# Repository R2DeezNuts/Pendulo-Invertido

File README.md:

# Péndulo invertido: control PID e interfaz web

Sistema de control PID para estabilizar un péndulo invertido con un ESP32. Incluye una interfaz web para ajustar los parámetros, telemetría y rutinas de calibración.

## Características

- Control PID a 100 Hz.
- Ajuste remoto de Kp, Ki, Kd, setpoint y offset.
- Calibración del ángulo cero.
- Desactivación automática cuando detecta una caída.
- Telemetría del estado del sistema.
- Anti-windup para limitar la acumulación del término integral.

## Hardware

- **Microcontrolador:** ESP32
- **Sensor inercial:** MPU6050 (acelerómetro y giroscopio)
- **Actuadores:** dos motores DC con puente H

### Conexiones GPIO

#### MPU6050 (I2C)

| Señal | GPIO |
|------:|:----:|
| SDA   | 21   |
| SCL   | 22   |

#### Motores (puente H)

| Motor | Señal | GPIO |
|------:|:-----:|
| A     | PWMA  | 26   |
| A     | AIN1  | 2    |
| A     | AIN2  | 0    |
| B     | PWMB  | 25   |
| B     | BIN1  | 16   |
| B     | BIN2  | 17   |

## Puesta en marcha

1. Conéctate a la red WiFi **RobotAP** (contraseña: 12345678).
2. Abre http://192.168.4.1 en el navegador.
3. Con el robot en posición vertical, calibra el ángulo cero antes de activar los motores.
4. Ajusta los parámetros PID desde la interfaz y activa el control.

## Parámetros ajustables

| Parámetro | Descripción |
|----------:|-------------|
| **Kp, Ki, Kd** | Constantes del controlador PID |
| **Setpoint** | Ángulo objetivo, en grados |
| **Offset** | Ajuste fino para la calibración |

## Protección y arquitectura

La protección desactiva el control cuando el ángulo supera los 30° durante más de un segundo. El control se ejecuta en una tarea de FreeRTOS a 100 Hz; el servidor web permite consultar el estado y cambiar los parámetros; y un filtro complementario combina el acelerómetro y el giroscopio para estimar el ángulo.

## Uso recomendado

Coloca el robot en vertical, calibra el sensor y empieza con valores PID conservadores. Activa los motores mientras observas la telemetría y ajusta el setpoint y el offset de forma gradual.

Si entra en modo de protección, revisa la calibración, el sentido de giro, la saturación del control y las vibraciones o el ruido del MPU6050.

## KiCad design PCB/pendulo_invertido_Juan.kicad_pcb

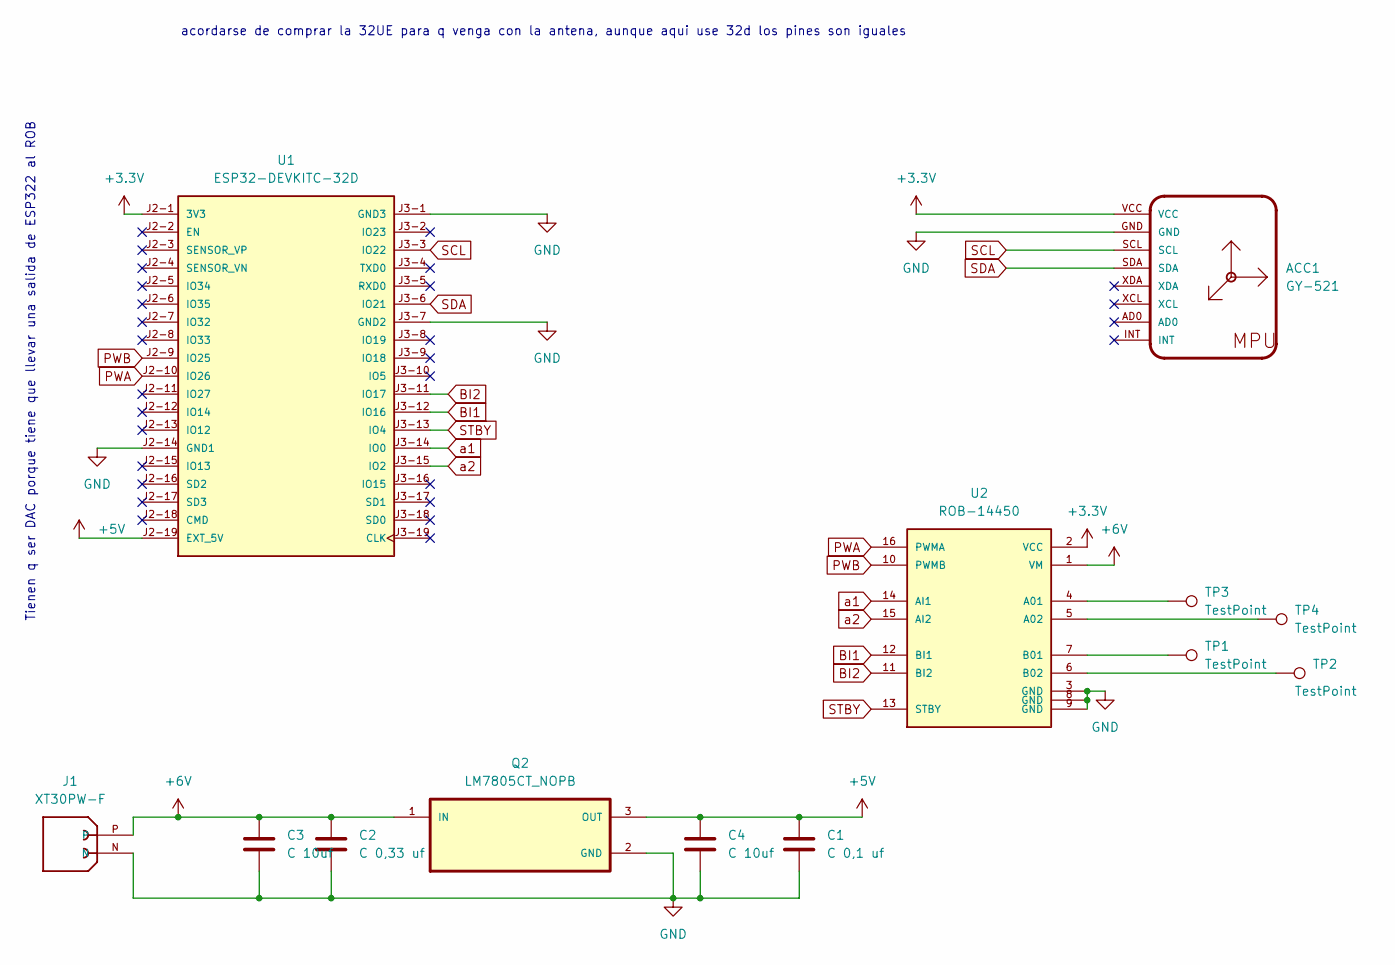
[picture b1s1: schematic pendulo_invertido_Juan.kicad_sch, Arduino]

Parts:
ACC1: GY-521
C1: C 0,1 uf; C_Disc_D4.3mm_W1.9mm_P5.00mm
C2: C 0,33 uf; C_Disc_D4.3mm_W1.9mm_P5.00mm
C3, C4: C 10uf; CP_Radial_D4.0mm_P2.00mm
J1: XT30PW-F; AMASS_XT30PW-F; PARTREV 1.2
Q2: LM7805CT_NOPB; TO254P1054X470X1955-3
TP1, TP2, TP3, TP4: TestPoint; TestPoint_THTPad_D2.0mm_Drill1.0mm
U1: ESP32-DEVKITC-32D; MODULE_ESP32-DEVKITC-32D; PARTREV V4
U2: ROB-14450; MODULE_ROB-14450; PARTREV 11-13-17

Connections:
+3.3V: ACC1.VCC, U1.J2-1 (3V3), U2.2 (VCC)
+5V: C1.1, C4.1, Q2.3 (OUT), U1.J2-19 (EXT_5V)
+6V: C2.1, C3.1, J1.P, Q2.1 (IN), U2.1 (VM)
BI1: U1.J3-12 (IO16), U2.12 (BI1)
BI2: U1.J3-11 (IO17), U2.11 (BI2)
GND: ACC1.GND, C1.2, C2.2, C3.2, C4.2, J1.N, Q2.2 (GND), U1.J2-14 (GND1), U1.J3-1 (GND3), U1.J3-7 (GND2), U2.3 (GND), U2.8 (GND), U2.9 (GND)
unnamed: TP3.1, U2.4 (A01)
unnamed: TP4.1, U2.5 (A02)
unnamed: TP1.1, U2.7 (B01)
unnamed: TP2.1, U2.6 (B02)
PWA: U1.J2-10 (IO26), U2.16 (PWMA)
PWB: U1.J2-9 (IO25), U2.10 (PWMB)
SCL: ACC1.SCL, U1.J3-3 (IO22)
SDA: ACC1.SDA, U1.J3-6 (IO21)
STBY: U1.J3-13 (IO4), U2.13 (STBY)
a1: U1.J3-14 (IO0), U2.14 (AI1)
a2: U1.J3-15 (IO2), U2.15 (AI2)

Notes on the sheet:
Tienen q ser DAC porque tiene que llevar una salida de ESP322 al ROB
acordarse de comprar la 32UE para q venga con la antena, aunque aqui use 32d los pines son iguales

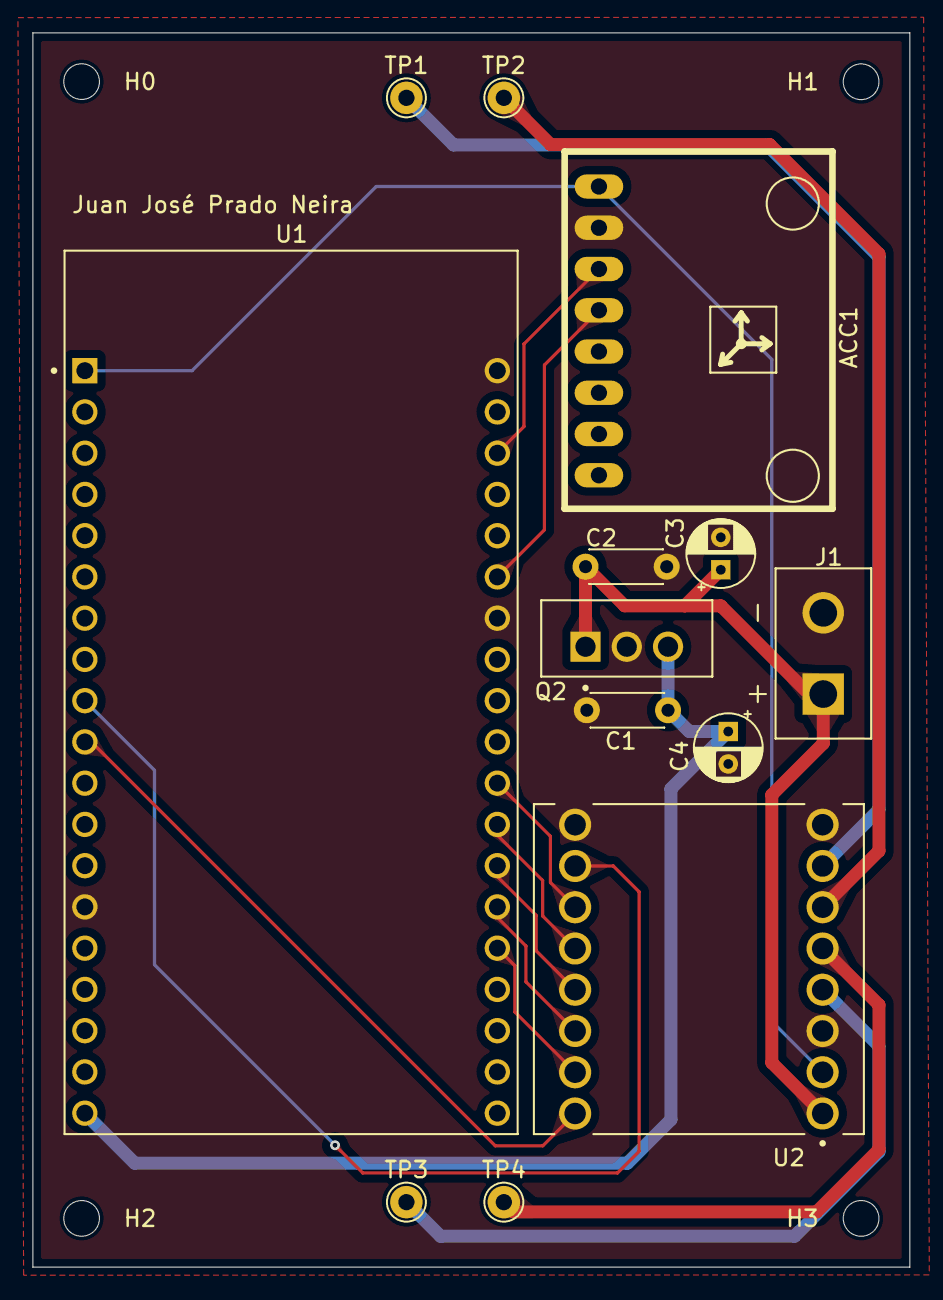
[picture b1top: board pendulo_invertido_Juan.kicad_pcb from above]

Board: 2 copper layers, 54.0 x 76.0 mm, 17 parts (0 on the bottom side), 17 nets.

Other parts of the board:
H0, H1, H2, H3: MountingHole_2.2mm_M2

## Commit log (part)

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2025-12-02 Comments
